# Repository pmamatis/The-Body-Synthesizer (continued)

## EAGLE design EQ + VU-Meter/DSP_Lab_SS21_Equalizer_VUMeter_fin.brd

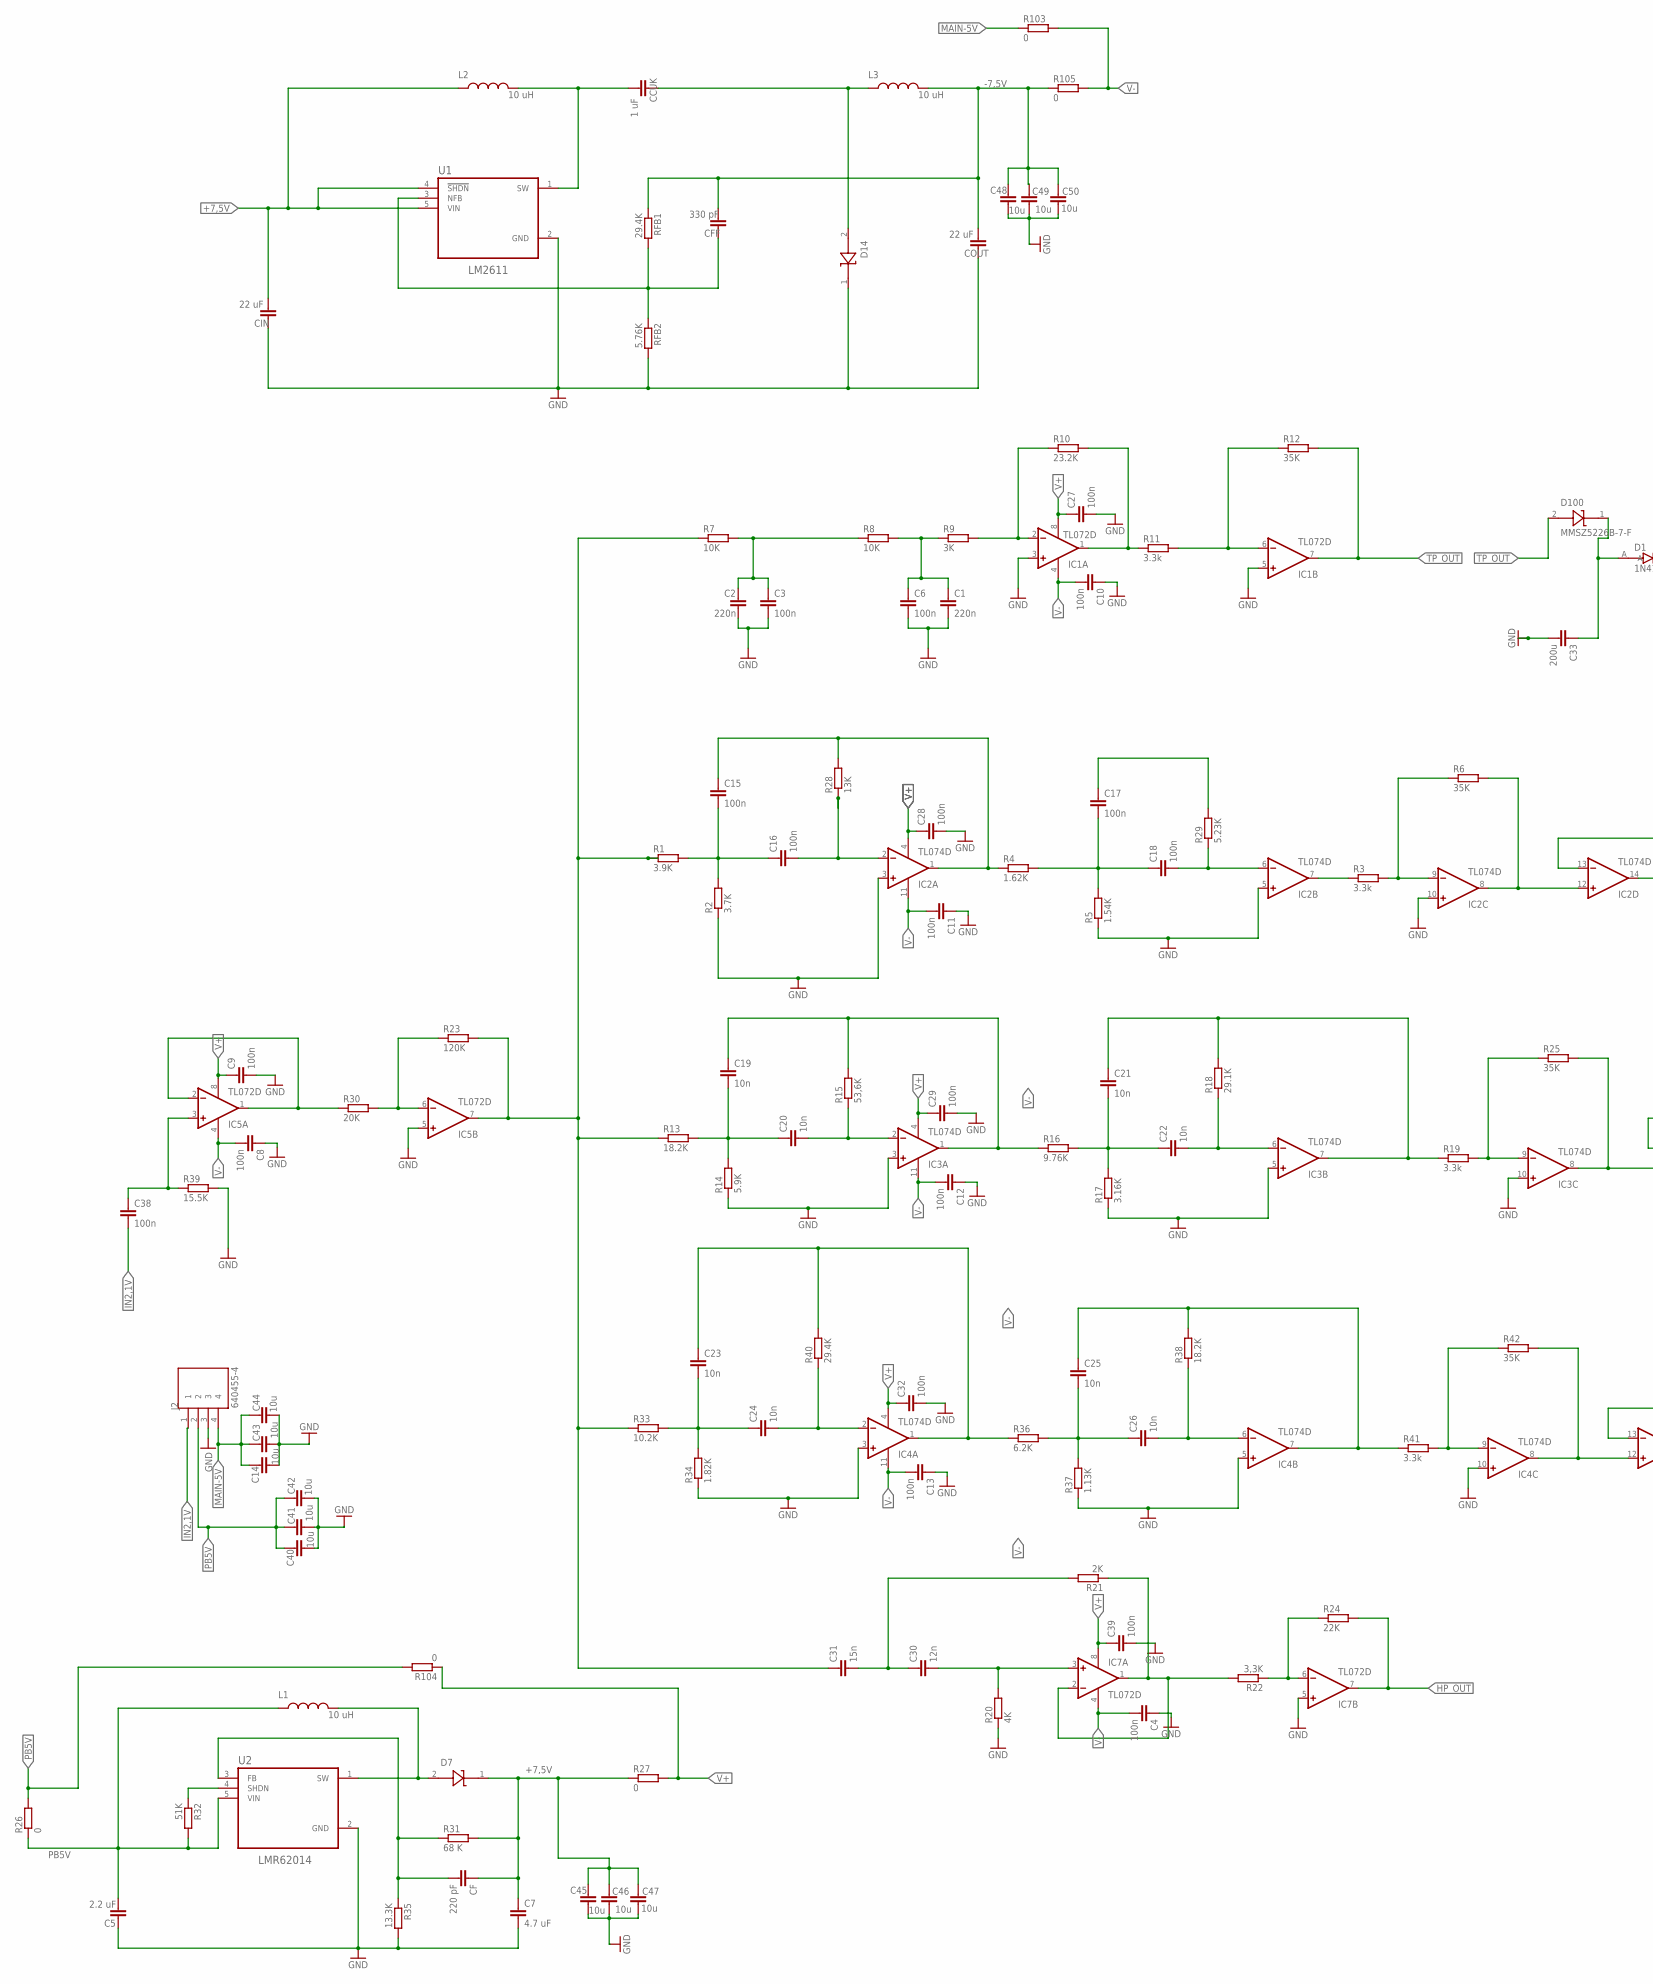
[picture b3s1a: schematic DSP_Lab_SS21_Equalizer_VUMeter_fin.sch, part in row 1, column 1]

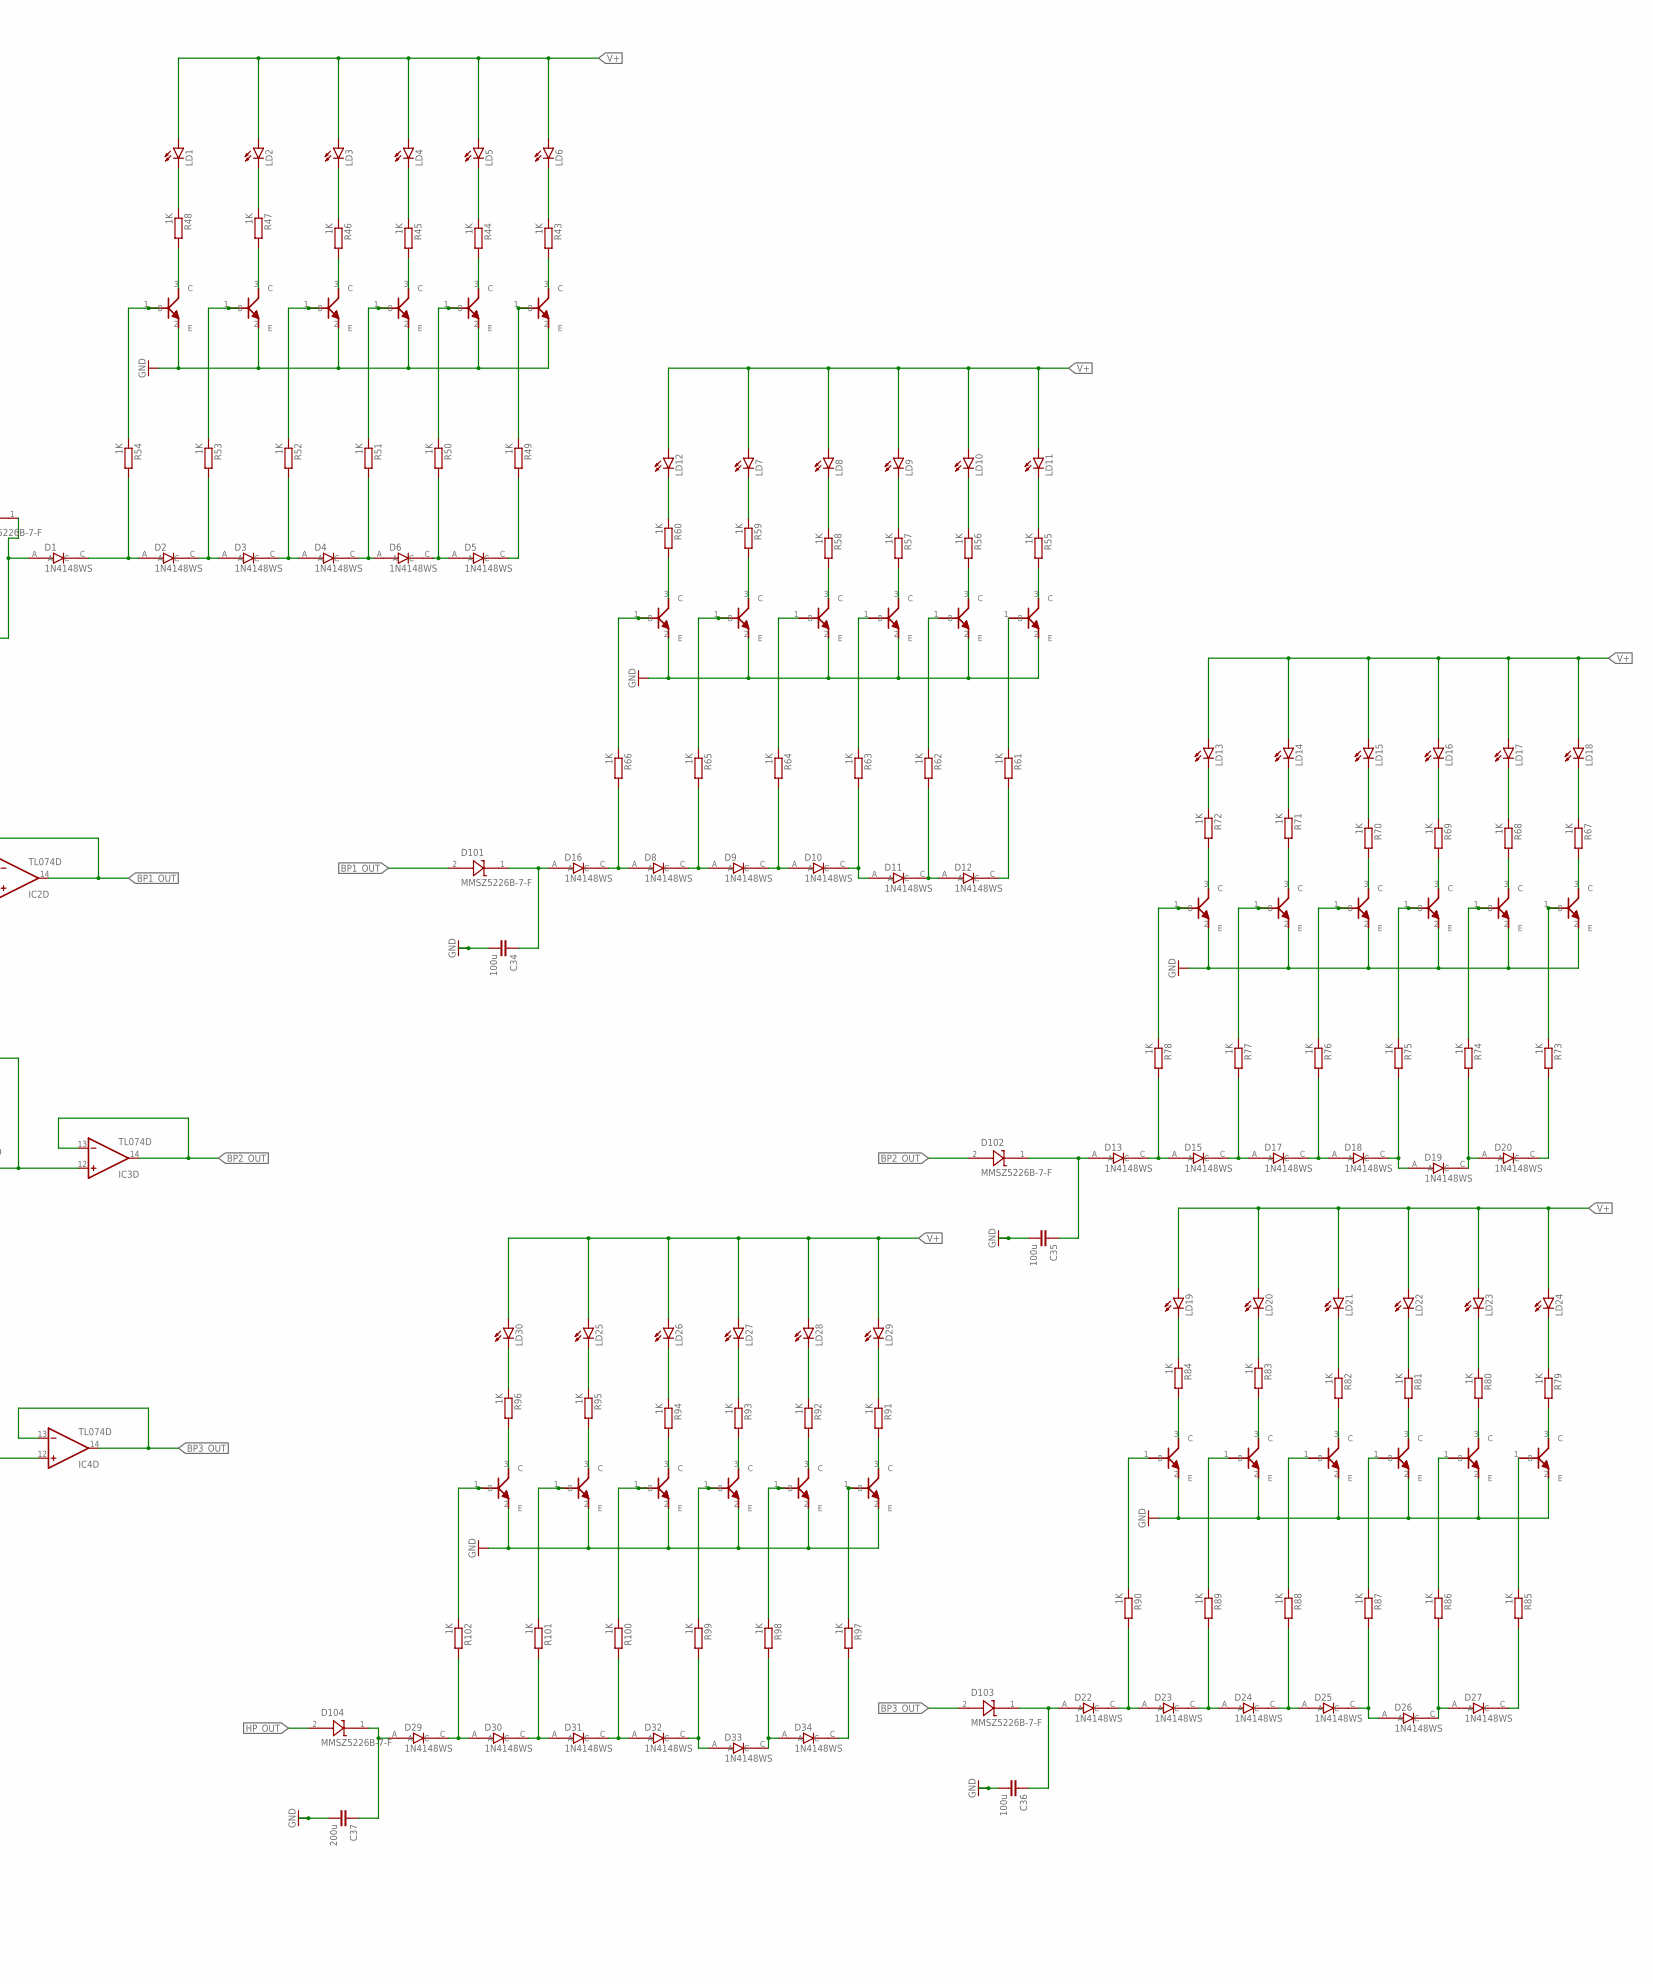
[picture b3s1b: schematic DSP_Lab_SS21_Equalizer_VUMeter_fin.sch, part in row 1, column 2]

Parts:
C1, C2: 220n; C0603
C3, C4, C6, C8, C9, C10, C11, C12, C13, C15, C16, C17, C18, C27, C28, C29, C32, C38, C39: 100n; C0603
C5: 2.2 uF; C0603
C7: 4.7 uF; C0603
C14, C40, C41, C42, C43, C44, C45, C46, C47, C48, C49, C50: 10u; C0603
C19, C20, C21, C22, C23, C24, C25, C26: 10n; C0603
C30: 12n; C0603
C31: 15n; C0603
C33, C37: 200u; C0603
C34, C35, C36: 100u; C0603
CCUK: 1 uF; C0603
CF: 220 pF; C0603
CFF: 330 pF; C0603
CIN: 22 uF; C0603
COUT: 22 uF; C0603
D1, D2, D3, D4, D5, D6, D8, D9, D10, D11, D12, D13, D15, D16, D17, D18, D19, D20, D22, D23, D24, D25, D26, D27, D29, D30, D31, D32, D33, D34: 1N4148WS; SODFL2512X100N
D7, D14, D100, D101, D102, D103, D104: MMSZ5226B-7-F; SOD3715X135L32X57N
IC1, IC5, IC7: TL072D; SO08
IC2, IC3, IC4: TL074D; SO14
J2: 640455-4; TE_640455-4
L1, L2, L3: 10 uH; INDC1608X95N
LD1, LD2, LD3, LD4, LD5, LD6, LD7, LD8, LD9, LD10, LD11, LD12, LD13, LD14, LD15, LD16, LD17, LD18, LD19, LD20, LD21, LD22, LD23, LD24, LD25, LD26, LD27, LD28, LD29, LD30: LEDCHIP-LED0603; CHIP-LED0603
R1: 3.9K; R0603
R2: 3.7K; R0603
R3, R11, R19, R41: 3.3k; R0603
R4: 1.62K; R0603
R5: 1.54K; R0603
R6, R12, R25, R42: 35K; R0603
R7, R8: 10K; R0603
R9: 3K; R0603
R10: 23.2K; R0603
R13, R38: 18.2K; R0603
R14: 5.9K; R0603
R15: 53,6K; R0603
R16: 9.76K; R0603
R17: 3.16K; R0603
R18: 29.1K; R0603
R20: 4K; R0603
R21: 2K; R0603
R22: 3,3K; R0603
R23: 120K; R0603
R24: 22K; R0603
R26, R27, R103, R104, R105: 0; R0603
R28: 13K; R0603
R29: 5.23K; R0603
R30: 20K; R0603
R31: 68 K; R0603
R32: 51K; R0603
R33: 10.2K; R0603
R34: 1.82K; R0603
R35: 13.3K; R0603
R36: 6.2K; R0603
R37: 1.13K; R0603
R39: 15.5K; R0603
R40: 29.4K; R0603
R43, R44, R45, R46, R47, R48, R49, R50, R51, R52, R53, R54, R55, R56, R57, R58, R59, R60, R61, R62, R63, R64, R65, R66, R67, R68, R69, R70, R71, R72, R73, R74, R75, R76, R77, R78, R79, R80, R81, R82, R83, R84, R85, R86, R87, R88, R89, R90, R91, R92, R93, R94, R95, R96, R97, R98, R99, R100, R101, R102: 1K; R0603
RFB1: 29.4K; R0603
RFB2: 5.76K; R0603
T1, T2, T3, T4, T5, T6, T7, T8, T9, T10, T11, T12, T13, T14, T15, T16, T17, T18, T19, T20, T21, T22, T23, T24, T25, T26, T27, T28, T29, T30: BC846A; SOT23-3
U1: LM2611; SOT95P280X145-5N
U2: LMR62014; SOT95P280X145-5N

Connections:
+7,5V: C7.1, C45.2, C46.1, C47.1, CF.1, CIN.1, D7.1 (C), L2.1, R27.1, R31.2, U1.4 (!SHDN), U1.5 (VIN)
-7,5V: C48.2, C49.1, C50.1, CFF.1, COUT.1, L3.2, R105.1, RFB1.1
BP1_OUT: D101.2 (A), IC2.13 (-IN), IC2.14 (OUT)
BP2_OUT: D102.2 (A), IC3.13 (-IN), IC3.14 (OUT)
BP3_OUT: D103.2 (A), IC4.13 (-IN), IC4.14 (OUT)
GND: C1.2, C2.2, C3.2, C4.1, C5.2, C6.2, C7.2, C8.1, C9.2, C10.1, C11.1, C12.1, C13.1, C14.1, C27.2, C28.2, C29.2, C32.2, C33.2, C34.2, C35.2, C36.2, C37.2, C39.2, C40.1, C41.2, C42.2, C43.2, C44.2, C45.1, C46.2, C47.2, C48.1, C49.2, C50.2, CIN.2, COUT.2, D14.1 (C), IC1.3 (+IN), IC1.5 (+IN), IC2.3 (+IN), IC2.5 (+IN), IC2.10 (+IN), IC3.3 (+IN), IC3.5 (+IN), IC3.10 (+IN), IC4.3 (+IN), IC4.5 (+IN), IC4.10 (+IN), IC5.5 (+IN), IC7.5 (+IN), J2.3, R2.1, R5.1, R14.1, R17.1, R20.1, R34.1, R35.2, R37.1, R39.2, RFB2.2, T1.2 (E), T2.2 (E), T3.2 (E), T4.2 (E), T5.2 (E), T6.2 (E), T7.2 (E), T8.2 (E), T9.2 (E), T10.2 (E), T11.2 (E), T12.2 (E), T13.2 (E), T14.2 (E), T15.2 (E), T16.2 (E), T17.2 (E), T18.2 (E), T19.2 (E), T20.2 (E), T21.2 (E), T22.2 (E), T23.2 (E), T24.2 (E), T25.2 (E), T26.2 (E), T27.2 (E), T28.2 (E), T29.2 (E), T30.2 (E), U1.2 (GND), U2.2 (GND)
HP_OUT: D104.2 (A), IC7.7 (OUT), R24.2
IN2,1V: C38.2, J2.1
MAIN-5V: C14.2, C43.1, C44.1, J2.4, R103.1
unnamed: C1.1, C6.1, R8.2, R9.1
unnamed: IC1.2 (-IN), R9.2, R10.1
unnamed: C2.1, C3.1, R7.2, R8.1
unnamed: C31.1, IC5.7 (OUT), R1.1, R7.1, R13.1, R23.2, R33.1
unnamed: IC2.9 (-IN), R3.2, R6.1
unnamed: IC1.1 (OUT), R10.2, R11.1
unnamed: IC3.9 (-IN), R19.2, R25.1
unnamed: IC1.6 (-IN), R11.2, R12.1
unnamed: C15.2, C16.1, R1.2, R2.2
unnamed: C16.2, IC2.2 (-IN), R28.1
unnamed: C15.1, IC2.1 (OUT), R4.1, R28.2
unnamed: C19.2, C20.1, R13.2, R14.2
unnamed: C17.1, R29.2
unnamed: C18.2, IC2.6 (-IN), R29.1
unnamed: C21.1, IC3.7 (OUT), R18.2, R19.1
unnamed: C20.2, IC3.2 (-IN), R15.1
unnamed: C19.1, IC3.1 (OUT), R15.2, R16.1
unnamed: R32.1, U2.4 (SHDN)
unnamed: CF.2, R31.1, R35.1, U2.3 (FB)
unnamed: C21.2, C22.1, R16.2, R17.2
unnamed: C22.2, IC3.6 (-IN), R18.1
unnamed: IC4.8 (OUT), IC4.12 (+IN), R42.2
unnamed: C23.1, IC4.1 (OUT), R36.1, R40.2
unnamed: C23.2, C24.1, R33.2, R34.2
unnamed: C24.2, IC4.2 (-IN), R40.1
unnamed: IC5.6 (-IN), R23.1, R30.2
unnamed: D15.C, D17.A, R77.2
unnamed: C25.2, C26.1, R36.2, R37.2
unnamed: C26.2, IC4.6 (-IN), R38.1
unnamed: D17.C, D18.A, R76.2
unnamed: C30.2, IC7.3 (+IN), R20.2
unnamed: C17.2, C18.1, R4.2, R5.2
unnamed: IC7.1 (OUT), IC7.2 (-IN), R21.1, R22.2
unnamed: D23.C, D24.A, R89.2
unnamed: C30.1, C31.2, R21.2
unnamed: IC7.6 (-IN), R22.1, R24.1
unnamed: LD6.C, R43.1
unnamed: LD5.C, R44.1
unnamed: IC5.1 (OUT), IC5.2 (-IN), R30.1
unnamed: LD4.C, R45.1
unnamed: LD3.C, R46.1
unnamed: LD2.C, R47.1
unnamed: LD1.C, R48.1
unnamed: C38.1, IC5.3 (+IN), R39.1
unnamed: C25.1, IC4.7 (OUT), R38.2, R41.1
unnamed: R43.2, T6.3 (C)
unnamed: R44.2, T5.3 (C)
unnamed: R45.2, T4.3 (C)
unnamed: R46.2, T3.3 (C)
unnamed: R47.2, T2.3 (C)
unnamed: R48.2, T1.3 (C)
unnamed: R49.1, T6.1 (B)
unnamed: R50.1, T5.1 (B)
unnamed: R51.1, T4.1 (B)
unnamed: R52.1, T3.1 (B)
unnamed: R53.1, T2.1 (B)
unnamed: R54.1, T1.1 (B)
unnamed: C33.1, D1.A, D100.1 (C)
unnamed: D1.C, D2.A, R54.2
unnamed: D2.C, D3.A, R53.2
unnamed: D3.C, D4.A, R52.2
unnamed: D4.C, D6.A, R51.2
unnamed: D5.A, D6.C, R50.2
unnamed: D5.C, R49.2
unnamed: LD11.C, R55.1
unnamed: LD10.C, R56.1
unnamed: LD9.C, R57.1
unnamed: LD8.C, R58.1
unnamed: LD7.C, R59.1
unnamed: LD12.C, R60.1
unnamed: D7.2 (A), L1.2, U2.1 (SW)
unnamed: R55.2, T7.3 (C)
unnamed: R56.2, T8.3 (C)
unnamed: R57.2, T9.3 (C)
unnamed: R58.2, T10.3 (C)
unnamed: R59.2, T11.3 (C)
unnamed: R60.2, T12.3 (C)
unnamed: R61.1, T7.1 (B)
unnamed: R62.1, T8.1 (B)
unnamed: R63.1, T9.1 (B)
unnamed: R64.1, T10.1 (B)
unnamed: R65.1, T11.1 (B)
unnamed: R66.1, T12.1 (B)
unnamed: C34.1, D16.A, D101.1 (C)
unnamed: D8.A, D16.C, R66.2
unnamed: D8.C, D9.A, R65.2
unnamed: D9.C, D10.A, R64.2
unnamed: D10.C, D11.A, R63.2
unnamed: D11.C, D12.A, R62.2
unnamed: D12.C, R61.2
unnamed: LD18.C, R67.1
unnamed: LD17.C, R68.1
unnamed: LD16.C, R69.1
unnamed: LD15.C, R70.1
unnamed: LD14.C, R71.1
unnamed: LD13.C, R72.1
unnamed: IC3.8 (OUT), IC3.12 (+IN), R25.2
unnamed: R67.2, T18.3 (C)
unnamed: R68.2, T17.3 (C)
unnamed: R69.2, T16.3 (C)
unnamed: R70.2, T15.3 (C)
unnamed: R71.2, T14.3 (C)
unnamed: R72.2, T13.3 (C)
unnamed: R73.1, T18.1 (B)
unnamed: R74.1, T17.1 (B)
unnamed: R75.1, T16.1 (B)
unnamed: R76.1, T15.1 (B)
unnamed: R77.1, T14.1 (B)
unnamed: R78.1, T13.1 (B)
unnamed: C35.1, D13.A, D102.1 (C)
unnamed: D13.C, D15.A, R78.2
unnamed: IC2.8 (OUT), IC2.12 (+IN), R6.2
unnamed: D18.C, D19.A, R75.2
unnamed: D19.C, D20.A, R74.2
unnamed: D20.C, R73.2
unnamed: LD24.C, R79.1
unnamed: LD23.C, R80.1
unnamed: LD22.C, R81.1
unnamed: LD21.C, R82.1
unnamed: LD20.C, R83.1
unnamed: LD19.C, R84.1
unnamed: CCUK.2, D14.2 (A), L3.1
unnamed: R79.2, T24.3 (C)
unnamed: R80.2, T23.3 (C)
unnamed: R81.2, T22.3 (C)
unnamed: R82.2, T21.3 (C)
unnamed: R83.2, T20.3 (C)
unnamed: R84.2, T19.3 (C)
unnamed: R85.1, T24.1 (B)
unnamed: R86.1, T23.1 (B)
unnamed: R87.1, T22.1 (B)
unnamed: R88.1, T21.1 (B)
unnamed: R89.1, T20.1 (B)
unnamed: R90.1, T19.1 (B)
unnamed: C36.1, D22.A, D103.1 (C)
unnamed: D22.C, D23.A, R90.2
unnamed: CCUK.1, L2.2, U1.1 (SW)
unnamed: D24.C, D25.A, R88.2
unnamed: D25.C, D26.A, R87.2
unnamed: D26.C, D27.A, R86.2
unnamed: D27.C, R85.2
unnamed: LD29.C, R91.1
unnamed: LD28.C, R92.1
unnamed: LD27.C, R93.1
unnamed: LD26.C, R94.1
unnamed: LD25.C, R95.1
unnamed: LD30.C, R96.1
unnamed: CFF.2, RFB1.2, RFB2.1, U1.3 (NFB)
unnamed: R91.2, T30.3 (C)
unnamed: R92.2, T29.3 (C)
unnamed: R93.2, T28.3 (C)
unnamed: R94.2, T27.3 (C)
unnamed: R95.2, T26.3 (C)
unnamed: R96.2, T25.3 (C)
unnamed: R97.1, T30.1 (B)
unnamed: R98.1, T29.1 (B)
unnamed: R99.1, T28.1 (B)
unnamed: R100.1, T27.1 (B)
unnamed: R101.1, T26.1 (B)
unnamed: R102.1, T25.1 (B)
unnamed: C37.1, D29.A, D104.1 (C)
unnamed: D29.C, D30.A, R102.2
unnamed: D30.C, D31.A, R101.2
unnamed: D31.C, D32.A, R100.2
unnamed: D32.C, D33.A, R99.2
unnamed: D33.C, D34.A, R98.2
unnamed: D34.C, R97.2
unnamed: IC2.7 (OUT), R3.1
unnamed: IC4.9 (-IN), R41.2, R42.1
PB5V: C5.1, C40.2, C41.1, C42.1, J2.2, L1.1, R26.1, R26.2, R32.2, R104.2, U2.5 (VIN)
TP_OUT: D100.2 (A), IC1.7 (OUT), R12.2
V+: C9.1, C27.1, C28.1, C29.1, C32.1, C39.1, IC1.8 (V+), IC2.4 (V+), IC3.4 (V+), IC4.4 (V+), IC5.8 (V+), IC7.8 (V+), LD1.A, LD2.A, LD3.A, LD4.A, LD5.A, LD6.A, LD7.A, LD8.A, LD9.A, LD10.A, LD11.A, LD12.A, LD13.A, LD14.A, LD15.A, LD16.A, LD17.A, LD18.A, LD19.A, LD20.A, LD21.A, LD22.A, LD23.A, LD24.A, LD25.A, LD26.A, LD27.A, LD28.A, LD29.A, LD30.A, R27.2, R104.1
V-: C4.2, C8.2, C10.2, C11.2, C12.2, C13.2, IC1.4 (V-), IC2.11 (V-), IC3.11 (V-), IC4.11 (V-), IC5.4 (V-), IC7.4 (V-), R103.2, R105.2

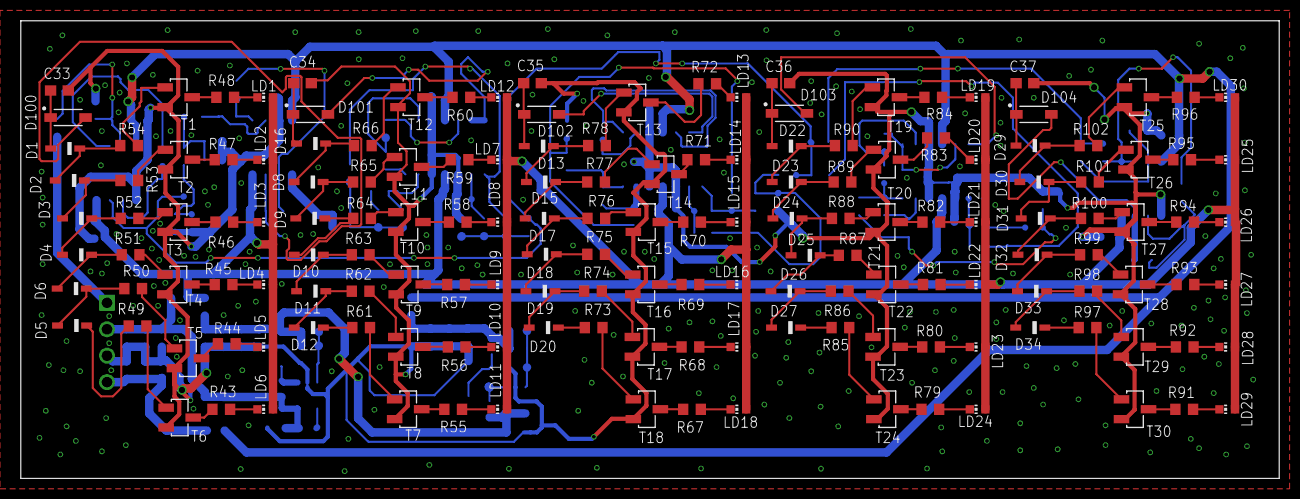
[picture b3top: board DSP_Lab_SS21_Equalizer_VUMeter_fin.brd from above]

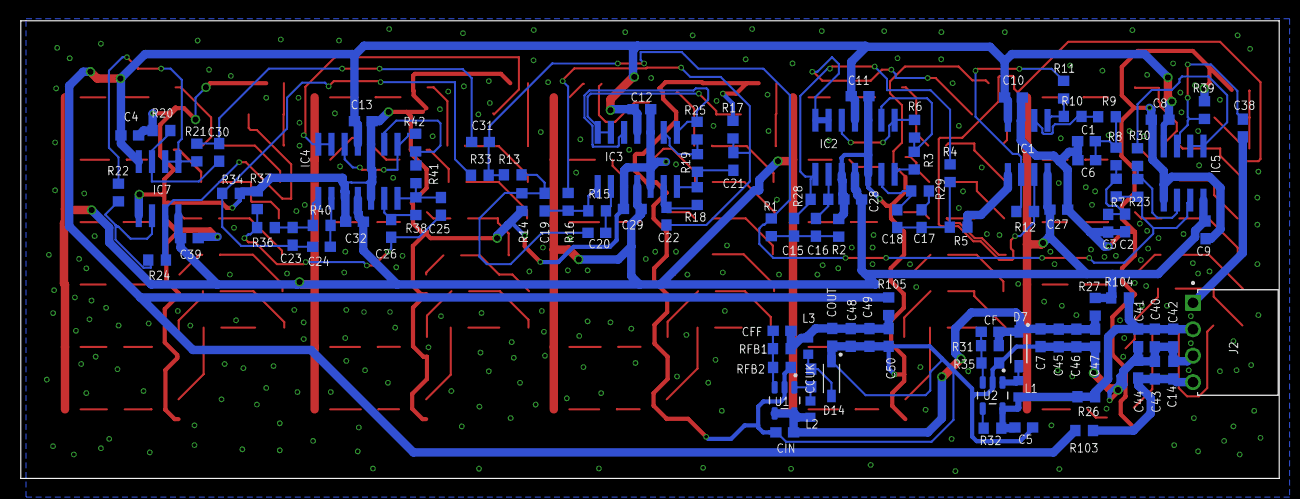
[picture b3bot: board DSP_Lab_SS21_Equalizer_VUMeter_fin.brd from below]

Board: 2 copper layers, 121.0 x 44.0 mm, 271 parts (111 on the bottom side), 182 nets.

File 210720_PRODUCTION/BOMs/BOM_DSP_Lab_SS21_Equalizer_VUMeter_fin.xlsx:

Qty | Value | Device | Package | Parts | Description | AVAILABILITY | CENTERLINE_PITCH | COMMENT | DESCRIPTION | MF | MP | NUMBER_OF_POSITIONS | PACKAGE | POPULARITY | PRICE | PRODUCT_TYPE | PURCHASE-URL | SPICEPREFIX
30 |  | LEDCHIP-LED0603 | CHIP-LED0603 | LD1, LD2, LD3, LD4, LD5, LD6, LD7, LD8, LD9, LD10, LD11, LD12, LD13, LD14, LD15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 | LED |  |  |  |  |  |  |  |  | 26
2 |  | MMSZ5226B-7-F | SOD3715X135L32X57N | D7, D14 | Diode Zener Single 3.3V 5% 500mW Automotive 2-Pin SOD-123 T/R Check prices | Good |  |  | Zener Diode 3.3V 500mW Â±5% Surface Mount SOD-123 | Diodes Inc. | MMSZ5226B-7-F |  | SOD-123 Diodes Inc. |  | None |  | https://pricing.snapeda.com/search/part/MMSZ5226B-7-F/?ref=eda
5 | 0 | R-EU_R0603 | R0603 | R26, R27, R103, R104, R105 | RESISTOR, European symbol
1 | 1 uF | C-EUC0603 | C0603 | CCUK | CAPACITOR, European symbol |  |  |  |  |  |  |  |  | 73 |  |  |  | C
1 | 1.13K | R-EU_R0603 | R0603 | R37 | RESISTOR, European symbol
1 | 1.54K | R-EU_R0603 | R0603 | R5 | RESISTOR, European symbol
1 | 1.62K | R-EU_R0603 | R0603 | R4 | RESISTOR, European symbol
1 | 1.82K | R-EU_R0603 | R0603 | R34 | RESISTOR, European symbol
3 | 10 uH | ASMCI-0603-100M-T | INDC1608X95N | L1, L2, L3 | MULTILAYER CHIP POWER INDUCTOR, 10UH, 50MA, CERAMIC, Â±20%, SHIELDED, 0.90 OHM,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 | Good |  |  | 10ÂµH Shielded Multilayer Inductor 50mA 900mOhm 0603 (1608 Metric) | Abracon LLC | ASMCI-0603-100M-T |  | 1608 Taiyo Yuden |  | None |  | https://pricing.snapeda.com/search/part/ASMCI-0603-100M-T/?ref=eda
1 | 10.2K | R-EU_R0603 | R0603 | R33 | RESISTOR, European symbol
1 | 100n | C-EUC0603 | C0603 | C38 | CAPACITOR, European symbol |  |  |  |  |  |  |  |  | 73 |  |  |  | C
18 | 100n | C-EUC0603 | C0603 | C3, C4, C6, C8, C9, C10, C11, C12, C13, C15, C16, C17, C18, C27, C28, C29, C32,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 | CAPACITOR, European symbol
3 | 100u | C-EUC0603 | C0603 | C34, C35, C36 | CAPACITOR, European symbol
2 | 10K | R-EU_R0603 | R0603 | R7, R8 | RESISTOR, European symbol
8 | 10n | C-EUC0603 | C0603 | C19, C20, C21, C22, C23, C24, C25, C26 | CAPACITOR, European symbol
12 | 10u | C-EUC0603 | C0603 | C14, C40, C41, C42, C43, C44, C45, C46, C47, C48, C49, C50 | CAPACITOR, European symbol
1 | 120K | R-EU_R0603 | R0603 | R23 | RESISTOR, European symbol
1 | 12n | C-EUC0603 | C0603 | C30 | CAPACITOR, European symbol
1 | 13.3K | R-EU_R0603 | R0603 | R35 | RESISTOR, European symbol
1 | 13K | R-EU_R0603 | R0603 | R28 | RESISTOR, European symbol
1 | 15.5K | R-EU_R0603 | R0603 | R39 | RESISTOR, European symbol
1 | 15n | C-EUC0603 | C0603 | C31 | CAPACITOR, European symbol
2 | 18.2K | R-EU_R0603 | R0603 | R13, R38 | RESISTOR, European symbol
60 | 1K | R-EU_R0603 | R0603 | R43, R44, R45, R46, R47, R48, R49, R50, R51, R52, R53, R54, R55, R56, R57, R58,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 | RESISTOR, European symbol
30 | 1N4148WS | 1N4148WS | SODFL2512X100N | D1, D2, D3, D4, D5, D6, D8, D9, D10, D11, D12, D13, D15, D16, D17, D18, D19, D2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 | 1N4148WS Series 75 V 300 mA Surface Mount Small Signal Diodes - SOD-323F Check 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 | Good |  |  | Diode Standard 75V 150mA Surface Mount SOD-323F | ON Semiconductor | 1N4148WS |  | SOD-323FL-2 ON Semiconductor |  | None |  | https://pricing.snapeda.com/search/part/1N4148WS/?ref=eda
1 | 2.2 uF | C-EUC0603 | C0603 | C5 | CAPACITOR, European symbol |  |  |  |  |  |  |  |  | 73 |  |  |  | C
2 | 200u | C-EUC0603 | C0603 | C33, C37 | CAPACITOR, European symbol
1 | 20K | R-EU_R0603 | R0603 | R30 | RESISTOR, European symbol
2 | 22 uF | C-EUC0603 | C0603 | CIN, COUT | CAPACITOR, European symbol |  |  |  |  |  |  |  |  | 73 |  |  |  | C
1 | 220 pF | C-EUC0603 | C0603 | CF | CAPACITOR, European symbol |  |  |  |  |  |  |  |  | 73 |  |  |  | C
2 | 220n | C-EUC0603 | C0603 | C1, C2 | CAPACITOR, European symbol
1 | 22K | R-EU_R0603 | R0603 | R24 | RESISTOR, European symbol
1 | 23.2K | R-EU_R0603 | R0603 | R10 | RESISTOR, European symbol
1 | 29.1K | R-EU_R0603 | R0603 | R18 | RESISTOR, European symbol
2 | 29.4K | R-EU_R0603 | R0603 | R40, RFB1 | RESISTOR, European symbol
1 | 2K | R-EU_R0603 | R0603 | R21 | RESISTOR, European symbol
1 | 3,3K | R-EU_R0603 | R0603 | R22 | RESISTOR, European symbol
1 | 3.16K | R-EU_R0603 | R0603 | R17 | RESISTOR, European symbol
4 | 3.3k | R-EU_R0603 | R0603 | R3, R11, R19, R41 | RESISTOR, European symbol
1 | 3.7K | R-EU_R0603 | R0603 | R2 | RESISTOR, European symbol
1 | 3.9K | R-EU_R0603 | R0603 | R1 | RESISTOR, European symbol
1 | 330 pF | C-EUC0603 | C0603 | CFF | CAPACITOR, European symbol |  |  |  |  |  |  |  |  | 73 |  |  |  | C
4 | 35K | R-EU_R0603 | R0603 | R6, R12, R25, R42 | RESISTOR, European symbol
1 | 3K | R-EU_R0603 | R0603 | R9 | RESISTOR, European symbol
1 | 4.7 uF | C-EUC0603 | C0603 | C7 | CAPACITOR, European symbol |  |  |  |  |  |  |  |  | 73 |  |  |  | C
1 | 4K | R-EU_R0603 | R0603 | R20 | RESISTOR, European symbol
1 | 5.23K | R-EU_R0603 | R0603 | R29 | RESISTOR, European symbol
1 | 5.76K | R-EU_R0603 | R0603 | RFB2 | RESISTOR, European symbol
1 | 5.9K | R-EU_R0603 | R0603 | R14 | RESISTOR, European symbol
1 | 51K | R-EU_R0603 | R0603 | R32 | RESISTOR, European symbol
1 | 53,6K | R-EU_R0603 | R0603 | R15 | RESISTOR, European symbol
1 | 6.2K | R-EU_R0603 | R0603 | R36 | RESISTOR, European symbol
1 | 640455-4 | 640455-4 | TE_640455-4 | J2 | Check prices | In Stock | 2.54 mm[.1 in] | 640455-4 | Headers & Receptacles cable a placa 8 POS MONO SHAPE MKII TAB ASS'Y GW 750.N TY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 | TE Connectivity | 640455-4 | 4 | None |  | None | Connector | https://pricing.snapeda.com/search/part/640455-4/?ref=eda
1 | 68 K | R-EU_R0603 | R0603 | R31 | RESISTOR, European symbol
1 | 9.76K | R-EU_R0603 | R0603 | R16 | RESISTOR, European symbol
29 | BC846A | BC846A | SOT23-3 | T1, T2, T3, T4, T5, T6, T7, T8, T9, T11, T12, T13, T14, T15, T16, T17, T18, T19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 |  | Unavailable |  |  | Bipolar (BJT) Transistor NPN 65V 100mA 100MHz 300mW Surface Mount SOT-23-3 (TO-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 | ON Semiconductor | BC846A |  | SOT-23-3 Motorola |  | None
1 | BC846A | BC846A | SOT23-3 | T10 |  | Unavailable |  |  | Bipolar (BJT) Transistor NPN 65V 100mA 100MHz 300mW Surface Mount SOT-23-3 (TO-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 | ON Semiconductor | BC846A |  | SOT-23-3 Motorola |  | None |  |  | J
1 | LM2611 | LM2611BMFX/NOPB | SOT95P280X145-5N | U1 | Check prices | Good |  |  | 1.4MHz Cuk Converter 5-SOT-23 -40 to 125 | Texas Instruments | LM2611BMFX/NOPB |  | SOT-23-5 Texas Instruments |  | None |  | https://pricing.snapeda.com/search/part/LM2611BMFX/NOPB/?ref=eda
1 | LMR62014 | LMR62014XMF/NOPB | SOT95P280X145-5N | U2 | Check prices | Good |  |  | SIMPLE SWITCHER&reg | 2.7V to 14V, 1.4A Step-Up Regulator in SOT-23 Package 5-SOT-23 -40 to 125 | Texas Instruments | LMR62014XMF/NOPB |  | SOT-23-5 Texas Instruments |  | None |  | https://pricing.snapeda.com/search/part/LMR62014XMF/NOPB/?ref=eda
5 | MMSZ5226B-7-F | MMSZ5226B-7-F | SOD3715X135L32X57N | D100, D101, D102, D103, D104 | Diode Zener Single 3.3V 5% 500mW Automotive 2-Pin SOD-123 T/R Check prices | Good |  |  | Zener Diode 3.3V 500mW Â±5% Surface Mount SOD-123 | Diodes Inc. | MMSZ5226B-7-F |  | SOD-123 Diodes Inc. |  | None |  | https://pricing.snapeda.com/search/part/MMSZ5226B-7-F/?ref=eda
3 | TL072D | TL072D | SO08 | IC1, IC5, IC7 | OP AMP |  |  |  |  |  |  |  |  | 0
3 | TL074D | TL074D | SO14 | IC2, IC3, IC4 | OP AMP |  |  |  |  |  |  |  |  | 0

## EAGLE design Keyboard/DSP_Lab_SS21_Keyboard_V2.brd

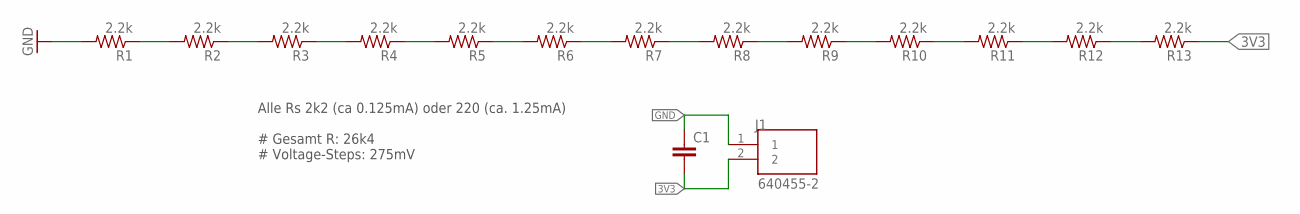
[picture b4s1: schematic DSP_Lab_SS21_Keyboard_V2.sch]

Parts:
C1: C-EUC0603; C0603
J1: 640455-2; TE_640455-2
R1, R2, R3, R4, R5, R6, R7, R8, R9, R10, R11, R12, R13: 2.2k; R0603

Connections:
3V3: C1.2, J1.2, R13.1
GND: C1.1, J1.1, R1.2
STEP1: R1.1, R2.2
STEP2: R2.1, R3.2
STEP3: R3.1, R4.2
STEP4: R4.1, R5.2
STEP5: R5.1, R6.2
STEP6: R6.1, R7.2
STEP7: R7.1, R8.2
STEP8: R8.1, R9.2
STEP9: R9.1, R10.2
STEP10: R10.1, R11.2
STEP11: R11.1, R12.2
STEP12: R12.1, R13.2

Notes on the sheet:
Alle Rs 2k2 (ca 0.125mA) oder 220 (ca. 1.25mA) # Gesamt R: 26k4 # Voltage-Steps: 275mV

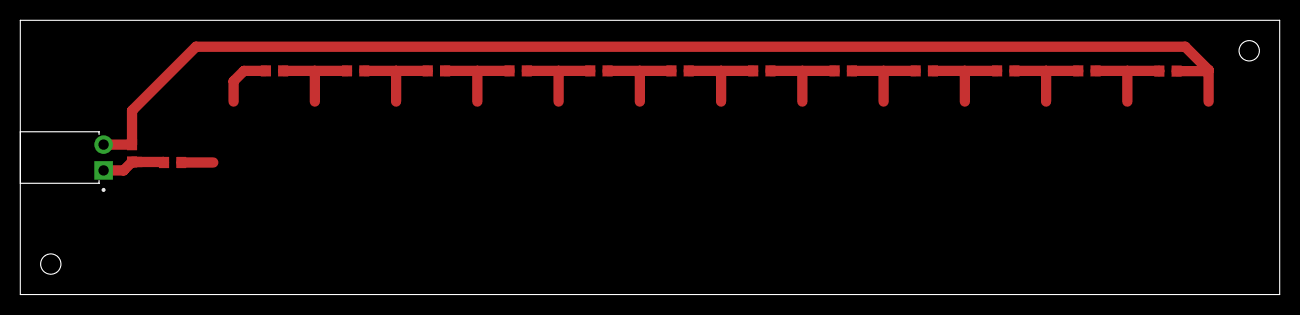
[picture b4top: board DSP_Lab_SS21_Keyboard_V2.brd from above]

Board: 2 copper layers, 124.0 x 27.0 mm, 15 parts (0 on the bottom side), 14 nets.

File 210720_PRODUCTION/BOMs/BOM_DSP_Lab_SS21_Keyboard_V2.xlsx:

Qty | Value | Device | Package | Parts | Description | AVAILABILITY | COMMENT | DESCRIPTION | EU_ROHS_COMPLIANCE | MF | MP | PACKAGE | POPULARITY | PRICE | SPICEPREFIX | TE_PURCHASE_URL
1 |  | C-EUC0603 | C0603 | C1 | CAPACITOR, European symbol |  |  |  |  |  |  |  | 73 |  | C
13 | 2.2k | R-US_R0603 | R0603 | R1, R2, R3, R4, R5, R6, R7, R8, R9, R10, R11, R12, R13 | RESISTOR, American symbol
1 | 640455-2 | 640455-2 | TE_640455-2 | J1 |  | Unavailable | 640455-2 | MTA-100 2 Position 2.54 mm Single Row Right Angle Wire to Board Header | Compliant | TE Connectivity | 640455-2 | None |  | None |  | https://www.te.com/usa-en/product-640455-2.html?te_bu=Cor&te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

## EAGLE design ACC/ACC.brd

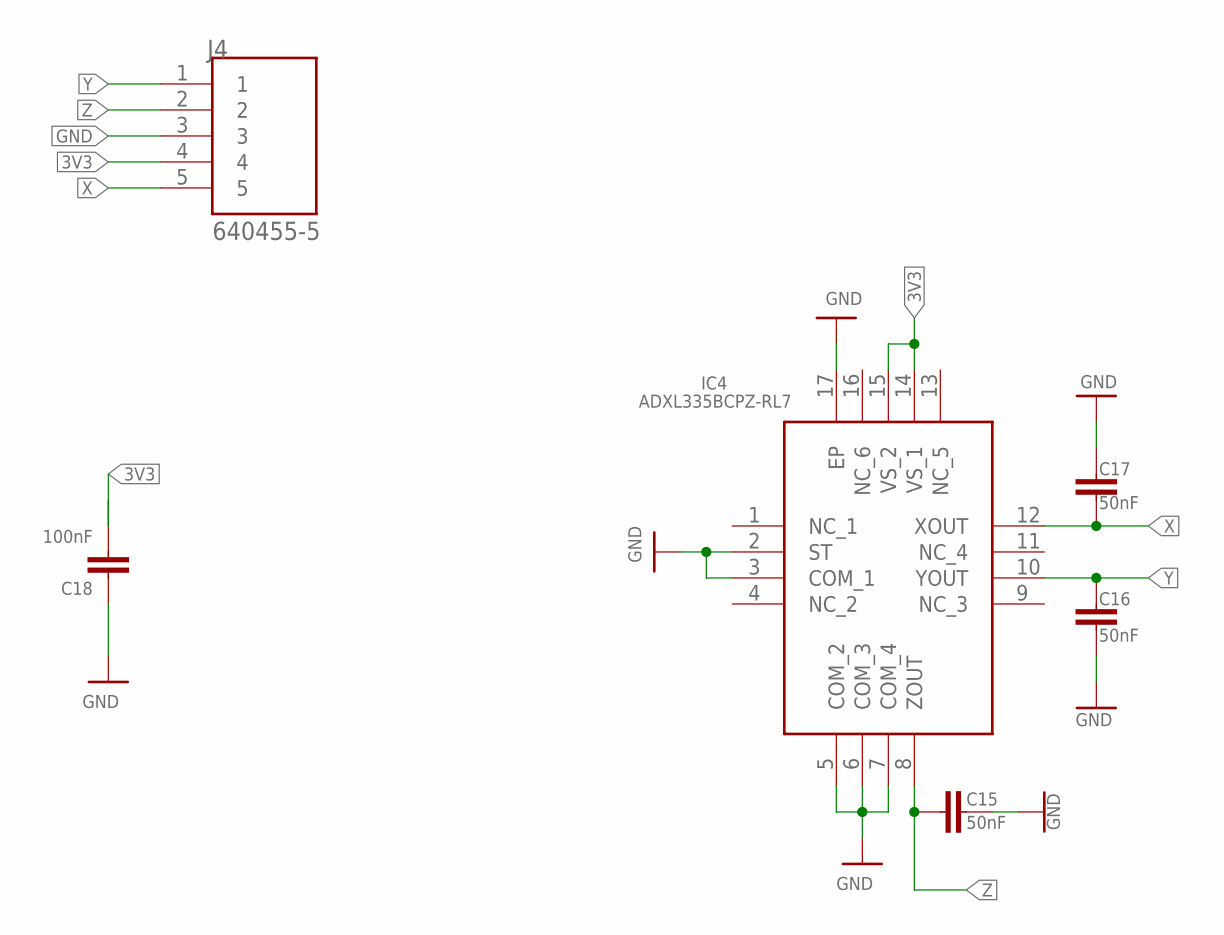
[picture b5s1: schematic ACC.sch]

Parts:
C15, C16, C17: 50nF; C0603
C18: 100nF; C0603
IC4: ADXL335BCPZ-RL7; QFN65P400X400X150-17N
J4: 640455-5; TE_640455-5

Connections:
3V3: C18.2, IC4.14 (VS_1), IC4.15 (VS_2), J4.4
GND: C15.1, C16.2, C17.1, C18.1, IC4.2 (ST), IC4.3 (COM_1), IC4.5 (COM_2), IC4.6 (COM_3), IC4.7 (COM_4), IC4.17 (EP), J4.3
X: C17.2, IC4.12 (XOUT), J4.5
Y: C16.1, IC4.10 (YOUT), J4.1
Z: C15.2, IC4.8 (ZOUT), J4.2

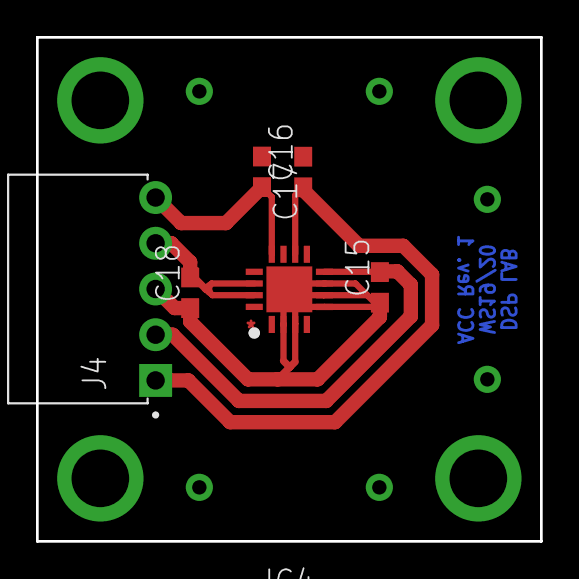
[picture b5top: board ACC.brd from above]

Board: 2 copper layers, 28.0 x 28.0 mm, 6 parts (0 on the bottom side), 5 nets.
